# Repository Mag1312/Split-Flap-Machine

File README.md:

# Split-Flap-Machine

This split flap machine is a hobby project by Mag, It is a device which displays time, date, weekday, weather, any word which is less than 7 letters and can even play your favourite songs from a MicroSD Card.

## Introduction

The Split Flap Machine's main attraction, The split flap consists of 37 flaps, 10 numbers (0-9), 26 alphabets (A-Z) and a blank flap. It is made possible mainly with the use of 28byj48 stepper motor, A4988 driver, Hall sensor and an ESP 32. The split flap drum has a small neodimium magnet which gets detected by the hall sensor and sends an update, the place where the magnet's field is not felt by the sensor, is the 0 position. Whenever something is to be displayed, the drum/spool is rotated with respect to this position to display.

The music system works from the webserver, where there are controls to play music. These controls can be used to play music from the MicroSD card.

This all works on a 10000MaH battery.

## Detailed Explanation

The split flap machine consists of 7 split flap units, consisting of 37 flaps, a spool and a stand. A single split flap unit uses a 28byj48 stepper motor, A4988 stepper driver, ky035 hall sensor and a ball bearing.
As mentioned earlier, after the startup a calibration function runs which runs in the following process.

Rotate spool until magnet detected --> Rotate spool until magnet is not detected --> set position = 0

After which to display a character, it first checks the ascii value of the character to be displayed in a seperate array, the position of the array of the ascii value is taken. the position of array times the number of steps per flap is multiplied to get the required position to revolve to display the character. Afterwhich the motor rotates the spool until the position is achieved. There is a killswitch if the spool rotates more than 1 revolution the program fails and freezes.

You can better understand this in my firmware, go check it out. This is the central operation around which all functions work.

The song system uses a MicroSD card, PCM5102A DAC Module, PAM8406 Amplifier and 2x 8ohm 3Watt speakers. This has been chosen for the highest quality and a mid-high battery life.

The system uses a 10000MaH battery pack with a buck converter to convert voltage.

#

Read Timeline.md for more understanding.

If you have any regards or have found an issue please contact +91 9346651359 (or) email to magazine2512@gmail.com.

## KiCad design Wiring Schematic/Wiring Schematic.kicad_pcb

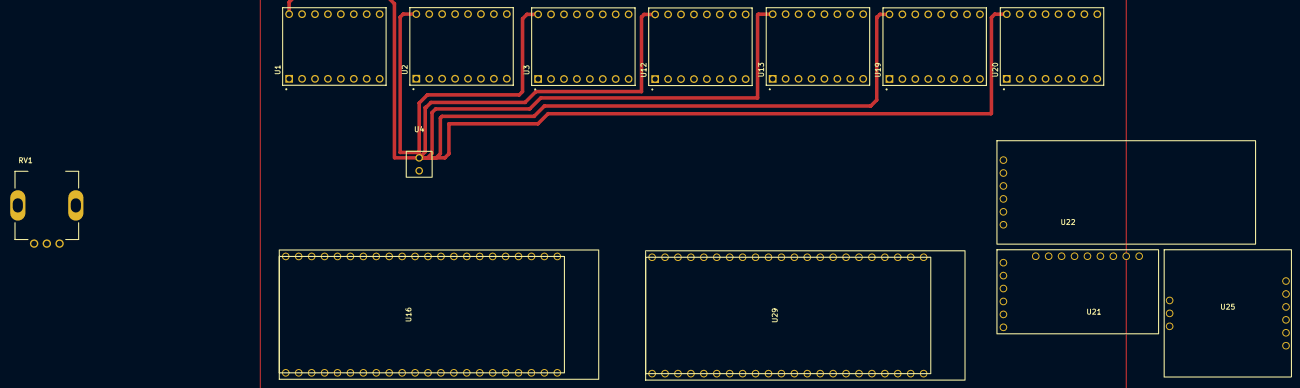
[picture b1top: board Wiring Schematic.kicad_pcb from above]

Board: 2 copper layers, 14 parts (0 on the bottom side), 29 nets.

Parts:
RV1: R_Potentiometer; XDCR_PEC11R-4215F-S0024
U1, U2, U3, U12, U13, U19, U20: MODULE_A4988_STEPPER_MOTOR_DRIVER_CARRIER
U4: Buck_Converter
U16, U29: ESP 32 S3 Devkit C1
U21: PCM5102A_DAC
U22: MicroSD_Module
U25: PAM_8406

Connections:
+3.3V: RV1.3, U1.RST (RESET), U1.VDD, U2.RST (RESET), U2.VDD, U3.RST (RESET), U3.VDD, U12.RST (RESET), U12.VDD, U13.RST (RESET), U13.VDD, U16.3V3, U19.RST (RESET), U19.VDD, U20.RST (RESET), U20.VDD, U21.VIN, U22.VCC, U29.3V3
+5V: U1.VMOT, U2.VMOT, U3.VMOT, U4.P_OUT(+), U12.VMOT, U13.VMOT, U16.5V (5V0), U19.VMOT, U20.VMOT, U25.VCC, U29.5V (5V0)
GND: RV1.1, U1.MS1, U1.MS2, U1.MS3, U2.MS1, U2.MS2, U2.MS3, U3.MS1, U3.MS2, U3.MS3, U4.P_OUT(-), U12.MS1, U12.MS2, U12.MS3, U13.MS1, U13.MS2, U13.MS3, U16.G (GND), U19.MS1, U19.MS2, U19.MS3, U20.MS1, U20.MS2, U20.MS3, U25.G (GND), U29.G (GND)
GPIO2 - ENB: U1.EN (ENABLE), U2.EN (ENABLE), U3.EN (ENABLE), U12.EN (ENABLE), U13.EN (ENABLE), U19.EN (ENABLE), U20.EN (ENABLE), U29.2 (GPIO2)
GPIO3 - SLP: U1.SLP (SLEEP), U2.SLP (SLEEP), U3.SLP (SLEEP), U12.SLP (SLEEP), U13.SLP (SLEEP), U19.SLP (SLEEP), U20.SLP (SLEEP), U29.3 (GPIO3)
GPIO4 - POT: RV1.2, U16.4 (GPIO4)
GPIO4 - S1: U1.STEP, U29.4 (GPIO4)
GPIO5 - D1: U1.DIR, U29.5 (GPIO5)
GPIO6 - BCK: U16.6 (GPIO6), U21.BCK
GPIO6 - S2: U12.STEP, U29.6 (GPIO6)
GPIO7 - D2: U12.DIR, U29.7 (GPIO7)
GPIO7 - LCK: U16.7 (GPIO7), U21.LCRK
GPIO8 - DIN: U16.8 (GPIO8), U21.DIN
GPIO8 - S3: U19.STEP, U29.8 (GPIO8)
GPIO9 - D3: U19.DIR, U29.9 (GPIO9)
GPIO10 - CS: U16.10 (GPIO10), U22.CS
GPIO10 - S4: U2.STEP, U29.10 (GPIO10)
GPIO11 - D4: U2.DIR, U29.11 (GPIO11)
GPIO11 - MOSI: U16.11 (GPIO11), U22.MOSI
GPIO12 - S5: U13.STEP, U29.12 (GPIO12)
GPIO12 - SCK: U16.12 (GPIO12), U22.SCK
GPIO13 - D5: U13.DIR, U29.13 (GPIO13)
GPIO13 - MISO: U16.13 (GPIO13), U22.MISO
GPIO14 - S6: U20.STEP, U29.14 (GPIO14)
GPIO15 - D6: U20.DIR, U29.15 (GPIO15)
GPIO16 - S7: U3.STEP, U29.16 (GPIO16)
GPIO17 - D7: U3.DIR, U29.17 (GPIO17)
LOUT- LIN: U21.LROUT, U25.LIN
ROUT - RIN: U21.ROUT, U25.RIN

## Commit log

2026-02-26 Day 2
2026-02-27 Day 3
2026-02-28 Day 4
2026-03-03 Day 6
2026-03-04 Day 7
2026-03-05 Day 8
2026-03-06 Day 9
2026-03-06 Revise README for clarity and detailed explanation
    Updated project description, added detailed explanation of components and functionality, and improved overall clarity.
2026-03-21 Review Commit
2026-05-02 Journal
2026-05-03 Add project documentation for Split Flap Machine
    Documented the creation process of a Split Flap Machine, including design updates, code implementations, and a final BOM list.
2026-05-03 Rename JOURNAL.md to Timeline.md
2026-05-03 Rename Journ.md to JOURNAL.md
